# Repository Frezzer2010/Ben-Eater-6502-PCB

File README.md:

# Ben-Eater-6502-PCB
My custom PCB designed to run Ben Eater's 6502 breadboard CPU with original memory map and wiring.

Why i made it:  
This PCB was primarily made because i didnt want to wire up my breadboard by hand, again. I wanted it to be portable with no loose wires, and easier to handle. I also wanted to stop having to go back and re-watch all the videos to figure out what was wrong when something did end up not working. So in the end i made 3 versions of this pcb soon to be more, each taking around a week or less.

What does it feature:  
The PCB has 8 SDIP Sockets for the 8 core components, these components are enough for complex programs like WOZMON and msBASIC
(w65c02 CPU, at28c256 ROM, cy62256 RAM, w65c22 VIA, 74hc00 or 74ls00 NAND, w65c51 ACIA, 1Mhz oscillator, 1.8432Mhz oscillator)
It has breakout ports for the CPU such as bus control, interupts, cpu halting, etc.
It also has nessesary ports like the DATA and ADDRESS bus, for adding new components such as extra 6522 VIAs, or VRAM.
and the most recent addition is the ACIA pins to add RS232 interface, which i ended up using a built in max3232 USB to rs232 cord, because the max232 I got in Ben Eaters kit kepted overheating when I powered up the board in the wrong order.
and of course it has the 6522 A and B ports.

What will i add in the future:  
I plan on creating a new PCB adding the Motorola 6845 crt controller and other decode logic for VGA interface.
I also want to create a plastic housing/protective case for better portabilty, and just asthetics.

I've taken huge insperation by Ben Eater and getting me hooked on retro hardware and understanding how CPU's and other electronics work. I love his videos and hope he continues with more, thank you if you've enjoyed taking a look at this PCB, and if you would like for me to continue.

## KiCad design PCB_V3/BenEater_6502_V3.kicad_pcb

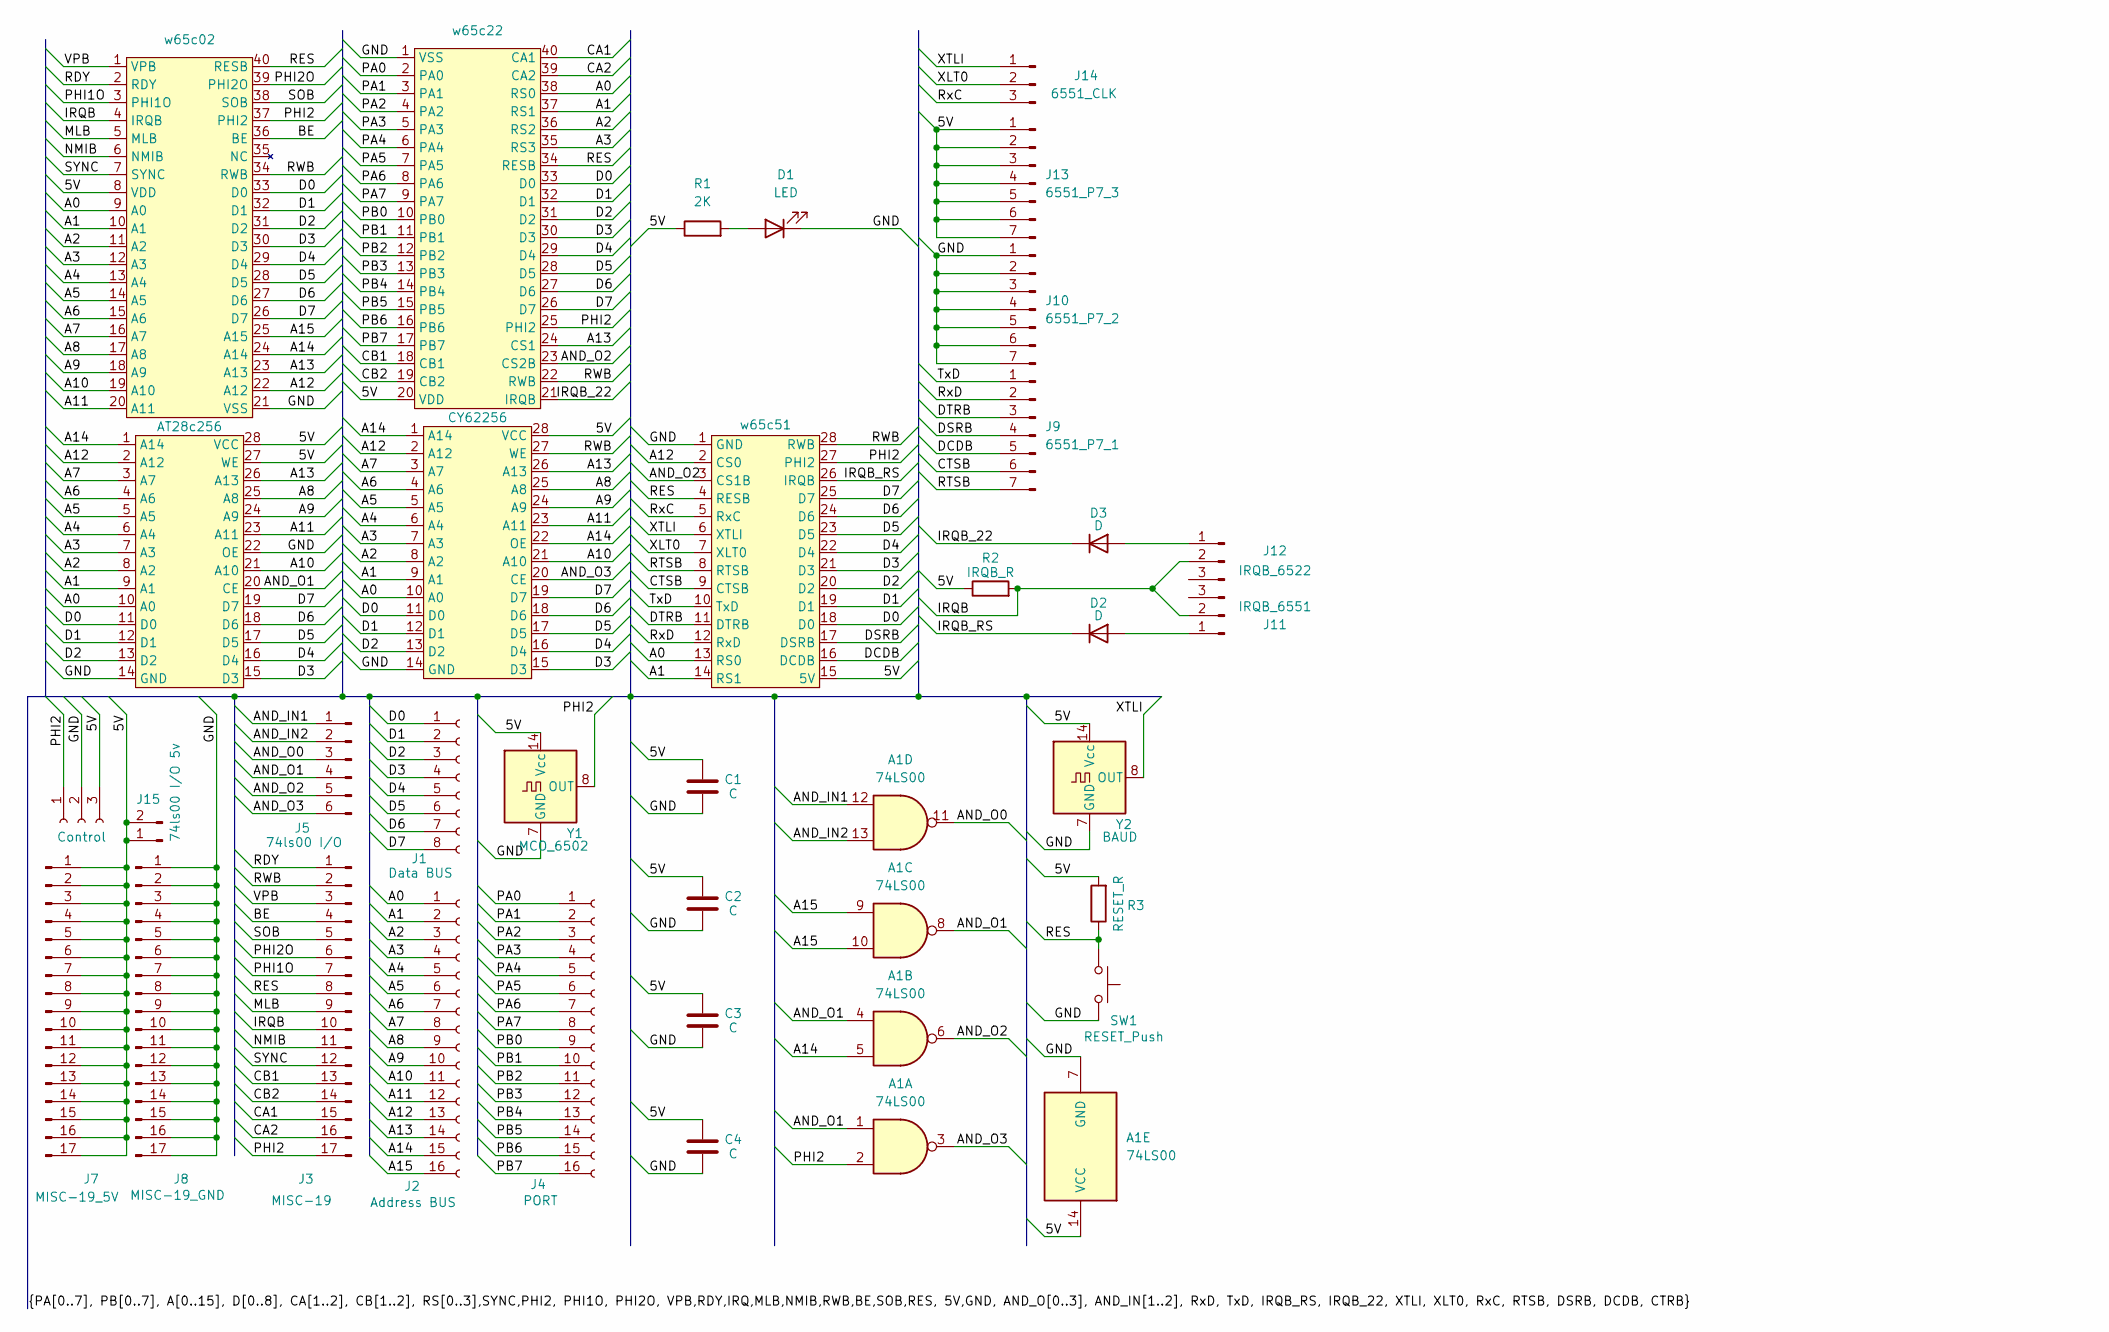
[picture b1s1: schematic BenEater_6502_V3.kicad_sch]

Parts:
A1: 74LS00; DIP-14_W7.62mm_Socket
C1, C2, C3, C4: C; C_Disc_D7.5mm_W2.5mm_P5.00mm
D1: LED; LED_D5.0mm
D2, D3: D; D_T-1_P5.08mm_Horizontal
J1: Data BUS; PinSocket_1x08_P2.54mm_Vertical
J2: Address BUS; PinSocket_1x16_P2.54mm_Vertical
J3: MISC-19; PinHeader_1x17_P2.54mm_Vertical
J4: PORT; PinSocket_1x16_P2.54mm_Vertical
J5: 74ls00 I/O; PinHeader_1x06_P2.54mm_Vertical
J6: Control; PinSocket_1x03_P2.54mm_Vertical
J7: MISC-19_5V; PinHeader_1x17_P2.54mm_Vertical
J8: MISC-19_GND; PinHeader_1x17_P2.54mm_Vertical
J9: 6551_P7_1; PinHeader_1x07_P2.54mm_Vertical
J10: 6551_P7_2; PinHeader_1x07_P2.54mm_Vertical
J11: IRQB_6551; PinHeader_1x03_P2.54mm_Vertical
J12: IRQB_6522; PinHeader_1x03_P2.54mm_Vertical
J13: 6551_P7_3; PinHeader_1x07_P2.54mm_Vertical
J14: 6551_CLK; PinHeader_1x03_P2.54mm_Vertical
J15: 74ls00 I/O 5v; PinHeader_1x02_P2.54mm_Vertical
R1: 2K; R_Axial_DIN0207_L6.3mm_D2.5mm_P7.62mm_Horizontal
R2: IRQB_R; R_Axial_DIN0207_L6.3mm_D2.5mm_P7.62mm_Horizontal
R3: RESET_R; R_Axial_DIN0207_L6.3mm_D2.5mm_P7.62mm_Horizontal
SW1: RESET_Push; SW_PUSH_6mm
U1: w65c02; DIP-40_W15.24mm_Socket
U2: w65c22; DIP-40_W15.24mm_Socket
U3: AT28c256; DIP-28_W15.24mm_Socket
U4: CY62256; DIP-28_W15.24mm_Socket
U5: w65c51; DIP-28_W15.24mm_Socket
Y1: MCO_6502; DIP-14_W7.62mm_Socket
Y2: BAUD; DIP-14_W7.62mm_Socket

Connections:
/5V: A1.14 (VCC), C1.2, C2.2, C3.2, C4.2, J6.3, J7.1, J7.2, J7.3, J7.4, J7.5, J7.6, J7.7, J7.8, J7.9, J7.10, J7.11, J7.12, J7.13, J7.14, J7.15, J7.16, J7.17, J13.1, J13.2, J13.3, J13.4, J13.5, J13.6, J13.7, J15.1, J15.2, R1.1, R2.1, R3.2, U1.8 (VDD), U2.20 (VDD), U3.27 (WE), U3.28 (VCC), U4.28 (VCC), U5.15 (5V), Y1.14 (Vcc), Y2.14 (Vcc)
/A0: J2.1, U1.9 (A0), U2.38 (RS0), U3.10 (A0), U4.10 (A0), U5.13 (RS0)
/A1: J2.2, U1.10 (A1), U2.37 (RS1), U3.9 (A1), U4.9 (A1), U5.14 (RS1)
/A2: J2.3, U1.11 (A2), U2.36 (RS2), U3.8 (A2), U4.8 (A2)
/A3: J2.4, U1.12 (A3), U2.35 (RS3), U3.7 (A3), U4.7 (A3)
/A4: J2.5, U1.13 (A4), U3.6 (A4), U4.6 (A4)
/A5: J2.6, U1.14 (A5), U3.5 (A5), U4.5 (A5)
/A6: J2.7, U1.15 (A6), U3.4 (A6), U4.4 (A6)
/A7: J2.8, U1.16 (A7), U3.3 (A7), U4.3 (A7)
/A8: J2.9, U1.17 (A8), U3.25 (A8), U4.25 (A8)
/A9: J2.10, U1.18 (A9), U3.24 (A9), U4.24 (A9)
/A10: J2.11, U1.19 (A10), U3.21 (A10), U4.21 (A10)
/A11: J2.12, U1.20 (A11), U3.23 (A11), U4.23 (A11)
/A12: J2.13, U1.22 (A12), U3.2 (A12), U4.2 (A12), U5.2 (CS0)
/A13: J2.14, U1.23 (A13), U2.24 (CS1), U3.26 (A13), U4.26 (A13)
/A14: A1.5, J2.15, U1.24 (A14), U3.1 (A14), U4.1 (A14), U4.22 (OE)
/A15: A1.9, A1.10, J2.16, U1.25 (A15)
/AND_IN1: A1.12, J5.1
/AND_IN2: A1.13, J5.2
/AND_O0: A1.11, J5.3
/AND_O1: A1.1, A1.4, A1.8, J5.4, U3.20 (CE)
/AND_O2: A1.6, J5.5, U2.23 (CS2B), U5.3 (CS1B)
/AND_O3: A1.3, J5.6, U4.20 (CE)
/BE: J3.4, U1.36 (BE)
/CA1: J3.15, U2.40 (CA1)
/CA2: J3.16, U2.39 (CA2)
/CB1: J3.13, U2.18 (CB1)
/CB2: J3.14, U2.19 (CB2)
/CTSB: J9.6, U5.9 (CTSB)
/D0: J1.1, U1.33 (D0), U2.33 (D0), U3.11 (D0), U4.11 (D0), U5.18 (D0)
/D1: J1.2, U1.32 (D1), U2.32 (D1), U3.12 (D1), U4.12 (D1), U5.19 (D1)
/D2: J1.3, U1.31 (D2), U2.31 (D2), U3.13 (D2), U4.13 (D2), U5.20 (D2)
/D3: J1.4, U1.30 (D3), U2.30 (D3), U3.15 (D3), U4.15 (D3), U5.21 (D3)
/D4: J1.5, U1.29 (D4), U2.29 (D4), U3.16 (D4), U4.16 (D4), U5.22 (D4)
/D5: J1.6, U1.28 (D5), U2.28 (D5), U3.17 (D5), U4.17 (D5), U5.23 (D5)
/D6: J1.7, U1.27 (D6), U2.27 (D6), U3.18 (D6), U4.18 (D6), U5.24 (D6)
/D7: J1.8, U1.26 (D7), U2.26 (D7), U3.19 (D7), U4.19 (D7), U5.25 (D7)
/DCDB: J9.5, U5.16 (DCDB)
/DSRB: J9.4, U5.17 (DSRB)
/DTRB: J9.3, U5.11 (DTRB)
/GND: A1.7 (GND), C1.1, C2.1, C3.1, C4.1, D1.1 (K), J6.2, J8.1, J8.2, J8.3, J8.4, J8.5, J8.6, J8.7, J8.8, J8.9, J8.10, J8.11, J8.12, J8.13, J8.14, J8.15, J8.16, J8.17, J10.1, J10.2, J10.3, J10.4, J10.5, J10.6, J10.7, SW1.2, U1.21 (VSS), U2.1 (VSS), U3.14 (GND), U3.22 (OE), U4.14 (GND), U5.1 (GND), Y1.7 (GND), Y2.7 (GND)
/IRQB: J3.10, J11.2, J12.2, R2.2, U1.4 (IRQB)
/IRQB_22: D3.1 (K), U2.21 (IRQB)
/IRQB_RS: D2.1 (K), U5.26 (IRQB)
/MLB: J3.9, U1.5 (MLB)
/NMIB: J3.11, U1.6 (NMIB)
/PA0: J4.1, U2.2 (PA0)
/PA1: J4.2, U2.3 (PA1)
/PA2: J4.3, U2.4 (PA2)
/PA3: J4.4, U2.5 (PA3)
/PA4: J4.5, U2.6 (PA4)
/PA5: J4.6, U2.7 (PA5)
/PA6: J4.7, U2.8 (PA6)
/PA7: J4.8, U2.9 (PA7)
/PB0: J4.9, U2.10 (PB0)
/PB1: J4.10, U2.11 (PB1)
/PB2: J4.11, U2.12 (PB2)
/PB3: J4.12, U2.13 (PB3)
/PB4: J4.13, U2.14 (PB4)
/PB5: J4.14, U2.15 (PB5)
/PB6: J4.15, U2.16 (PB6)
/PB7: J4.16, U2.17 (PB7)
/PHI1O: J3.7, U1.3 (PHI1O)
/PHI2: A1.2, J3.17, J6.1, U1.37 (PHI2), U2.25 (PHI2), U5.27 (PHI2), Y1.8 (OUT)
/PHI2O: J3.6, U1.39 (PHI2O)
/RDY: J3.1, U1.2 (RDY)
/RES: J3.8, R3.1, SW1.1, U1.40 (RESB), U2.34 (RESB), U5.4 (RESB)
/RTSB: J9.7, U5.8 (RTSB)
/RWB: J3.2, U1.34 (RWB), U2.22 (RWB), U4.27 (WE), U5.28 (RWB)
/RxC: J14.3, U5.5 (RxC)
/RxD: J9.2, U5.12 (RxD)
/SOB: J3.5, U1.38 (SOB)
/SYNC: J3.12, U1.7 (SYNC)
/TxD: J9.1, U5.10 (TxD)
/VPB: J3.3, U1.1 (VPB)
/XLT0: J14.2, U5.7 (XLT0)
/XTLI: J14.1, U5.6 (XTLI), Y2.8 (OUT)
unnamed: D1.2 (A), R1.2
unnamed: D2.2 (A), J11.1
unnamed: D3.2 (A), J12.1

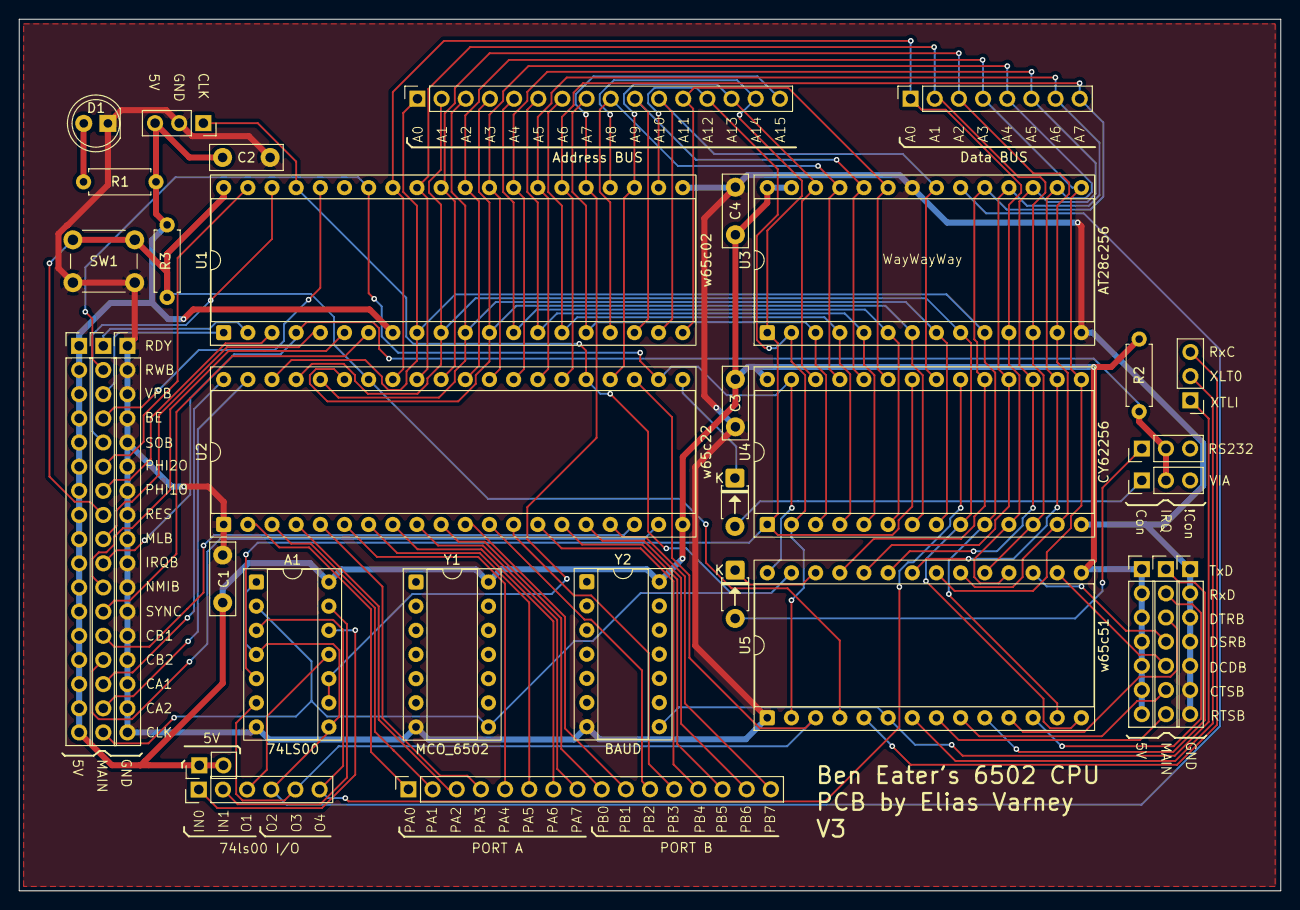
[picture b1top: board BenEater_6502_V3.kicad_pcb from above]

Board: 2 copper layers, 132.6 x 91.6 mm, 34 parts (0 on the bottom side), 80 nets.

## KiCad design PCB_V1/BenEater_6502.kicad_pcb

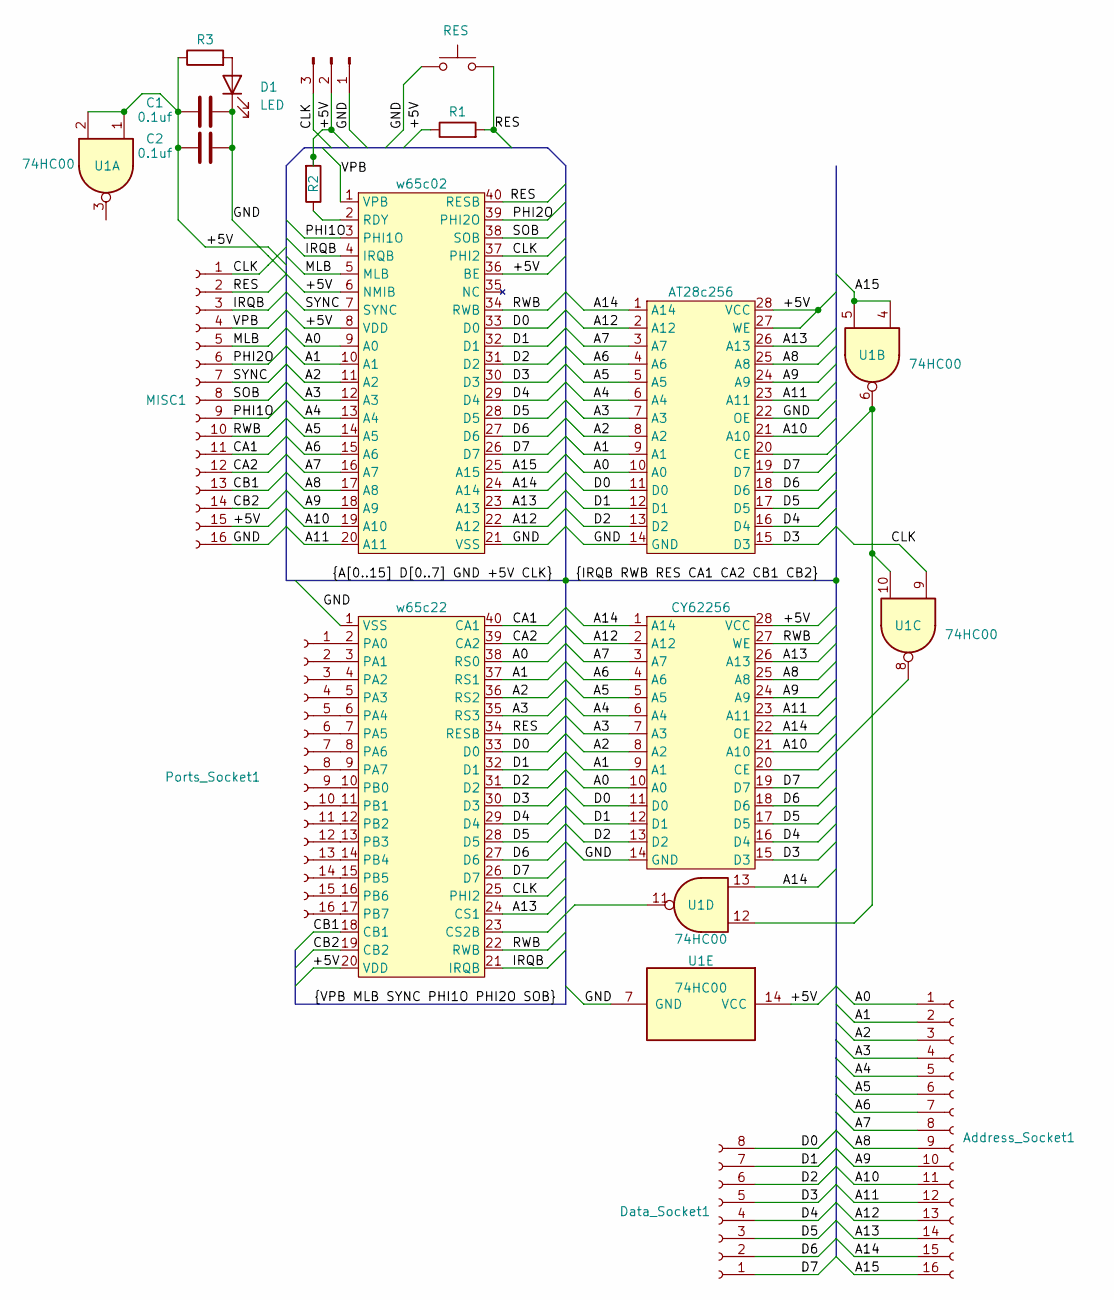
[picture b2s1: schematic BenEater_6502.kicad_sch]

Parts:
Address_Socket1: Conn_01x16_Socket; PinSocket_1x16_P2.54mm_Vertical
C1, C2: 0.1uf; C_Disc_D7.5mm_W2.5mm_P5.00mm
D1: LED; LED_D3.0mm
Data_Socket1: Conn_01x08_Socket; PinSocket_1x08_P2.54mm_Vertical
J1: Conn_01x03_Pin; PinSocket_1x03_P2.54mm_Vertical
MISC1: Conn_01x16_Socket; PinSocket_1x16_P2.54mm_Vertical
Ports_Socket1: Conn_01x16_Socket; PinSocket_1x16_P2.54mm_Vertical
R1, R2, R3: 1k; R_Axial_DIN0207_L6.3mm_D2.5mm_P10.16mm_Horizontal
SW1: RES; SW_PUSH_6mm
U1: 74HC00; DIP-14_W7.62mm_Socket
U2: w65c02; DIP-40_W15.24mm_Socket
U3: w65c22; DIP-40_W15.24mm_Socket
U4: CY62256; DIP-28_W15.24mm_Socket
U5: AT28c256; DIP-28_W15.24mm_Socket

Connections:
/+5V: C1.2, C2.2, J1.2, MISC1.15, R1.1, R2.2, R3.1, U1.1, U1.2, U1.14 (VCC), U2.6 (NMIB), U2.8 (VDD), U2.36 (BE), U3.20 (VDD), U4.28 (VCC), U5.27 (WE), U5.28 (VCC)
/A0: Address_Socket1.1, U2.9 (A0), U3.38 (RS0), U4.10 (A0), U5.10 (A0)
/A1: Address_Socket1.2, U2.10 (A1), U3.37 (RS1), U4.9 (A1), U5.9 (A1)
/A2: Address_Socket1.3, U2.11 (A2), U3.36 (RS2), U4.8 (A2), U5.8 (A2)
/A3: Address_Socket1.4, U2.12 (A3), U3.35 (RS3), U4.7 (A3), U5.7 (A3)
/A4: Address_Socket1.5, U2.13 (A4), U4.6 (A4), U5.6 (A4)
/A5: Address_Socket1.6, U2.14 (A5), U4.5 (A5), U5.5 (A5)
/A6: Address_Socket1.7, U2.15 (A6), U4.4 (A6), U5.4 (A6)
/A7: Address_Socket1.8, U2.16 (A7), U4.3 (A7), U5.3 (A7)
/A8: Address_Socket1.9, U2.17 (A8), U4.25 (A8), U5.25 (A8)
/A9: Address_Socket1.10, U2.18 (A9), U4.24 (A9), U5.24 (A9)
/A10: Address_Socket1.11, U2.19 (A10), U4.21 (A10), U5.21 (A10)
/A11: Address_Socket1.12, U2.20 (A11), U4.23 (A11), U5.23 (A11)
/A12: Address_Socket1.13, U2.22 (A12), U4.2 (A12), U5.2 (A12)
/A13: Address_Socket1.14, U2.23 (A13), U3.24 (CS1), U4.26 (A13), U5.26 (A13)
/A14: Address_Socket1.15, U1.13, U2.24 (A14), U4.1 (A14), U4.22 (OE), U5.1 (A14)
/A15: Address_Socket1.16, U1.4, U1.5, U2.25 (A15)
/CA1: MISC1.11, U3.40 (CA1)
/CA2: MISC1.12, U3.39 (CA2)
/CB1: MISC1.13, U3.18 (CB1)
/CB2: MISC1.14, U3.19 (CB2)
/CLK: J1.3, MISC1.1, U1.9, U2.37 (PHI2), U3.25 (PHI2)
/D0: Data_Socket1.8, U2.33 (D0), U3.33 (D0), U4.11 (D0), U5.11 (D0)
/D1: Data_Socket1.7, U2.32 (D1), U3.32 (D1), U4.12 (D1), U5.12 (D1)
/D2: Data_Socket1.6, U2.31 (D2), U3.31 (D2), U4.13 (D2), U5.13 (D2)
/D3: Data_Socket1.5, U2.30 (D3), U3.30 (D3), U4.15 (D3), U5.15 (D3)
/D4: Data_Socket1.4, U2.29 (D4), U3.29 (D4), U4.16 (D4), U5.16 (D4)
/D5: Data_Socket1.3, U2.28 (D5), U3.28 (D5), U4.17 (D5), U5.17 (D5)
/D6: Data_Socket1.2, U2.27 (D6), U3.27 (D6), U4.18 (D6), U5.18 (D6)
/D7: Data_Socket1.1, U2.26 (D7), U3.26 (D7), U4.19 (D7), U5.19 (D7)
/GND: C1.1, C2.1, D1.1 (K), J1.1, MISC1.16, SW1.1, U1.7 (GND), U2.21 (VSS), U3.1 (VSS), U4.14 (GND), U5.14 (GND), U5.22 (OE)
/IRQB: MISC1.3, U2.4 (IRQB), U3.21 (IRQB)
/MLB: MISC1.5, U2.5 (MLB)
/PHI1O: MISC1.9, U2.3 (PHI1O)
/PHI2O: MISC1.6, U2.39 (PHI2O)
/RES: MISC1.2, R1.2, SW1.2, U2.40 (RESB), U3.34 (RESB)
/RWB: MISC1.10, U2.34 (RWB), U3.22 (RWB), U4.27 (WE)
/SOB: MISC1.8, U2.38 (SOB)
/SYNC: MISC1.7, U2.7 (SYNC)
/VPB: MISC1.4, U2.1 (VPB)
unnamed: D1.2 (A), R3.2
unnamed: Ports_Socket1.1, U3.2 (PA0)
unnamed: Ports_Socket1.2, U3.3 (PA1)
unnamed: Ports_Socket1.3, U3.4 (PA2)
unnamed: Ports_Socket1.4, U3.5 (PA3)
unnamed: Ports_Socket1.5, U3.6 (PA4)
unnamed: Ports_Socket1.6, U3.7 (PA5)
unnamed: Ports_Socket1.7, U3.8 (PA6)
unnamed: Ports_Socket1.8, U3.9 (PA7)
unnamed: Ports_Socket1.9, U3.10 (PB0)
unnamed: Ports_Socket1.10, U3.11 (PB1)
unnamed: Ports_Socket1.11, U3.12 (PB2)
unnamed: Ports_Socket1.12, U3.13 (PB3)
unnamed: Ports_Socket1.13, U3.14 (PB4)
unnamed: Ports_Socket1.14, U3.15 (PB5)
unnamed: Ports_Socket1.15, U3.16 (PB6)
unnamed: Ports_Socket1.16, U3.17 (PB7)
unnamed: R2.1, U2.2 (RDY)
unnamed: U1.11, U3.23 (CS2B)
unnamed: U1.8, U4.20 (CE)
unnamed: U1.6, U1.10, U1.12, U5.20 (CE)

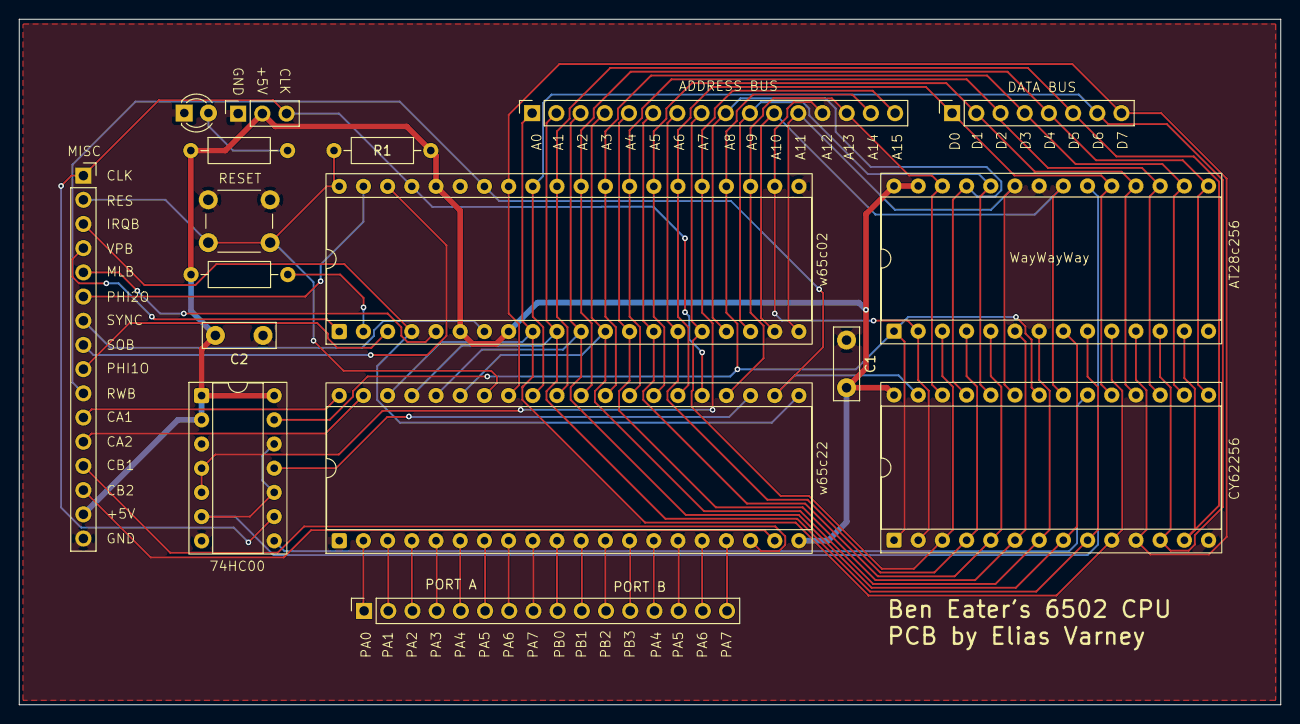
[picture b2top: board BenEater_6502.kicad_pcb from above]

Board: 2 copper layers, 132.4 x 72.0 mm, 17 parts (0 on the bottom side), 61 nets.
